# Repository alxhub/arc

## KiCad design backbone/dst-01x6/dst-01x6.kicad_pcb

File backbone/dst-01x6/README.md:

# ARC-DST-01x6

ARC-DST-01x6 drives six independent track districts from the layout's track supply. It receives DCC timing over the ARC backbone, while CAN carries commands and reports each district's state.

Each district can drive normal train traffic or a programming track at a lower current limit. The board measures its total track current and each district's current, so ARC can identify an overloaded section. Two temperature sensors and a controlled fan support sustained operation.

The six district board serves larger sections of a layout with one controller and one backbone connection. Its link is electrically isolated from the track supply, and its DC input protects against a reversed field connection.

[Board design](board.kdl)
[PCB layout](dst-01x6.kicad_pcb)

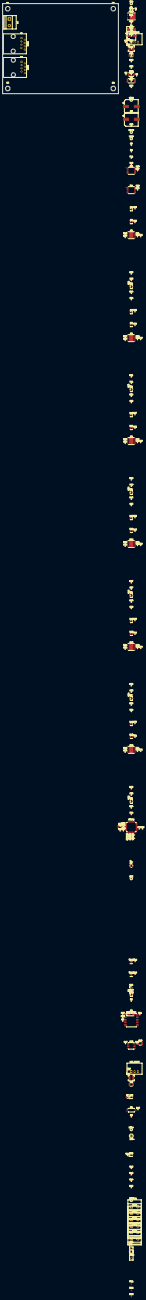
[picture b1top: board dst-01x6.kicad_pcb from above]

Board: 4 copper layers, 90.0 x 70.0 mm, 216 parts (0 on the bottom side), 142 nets, no tracks yet.

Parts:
3V3_BUCK: R-78K3.3-0.5; Converter_DCDC_RECOM_R-78K-0.5_THT
C1, C33, C41, C49, C57, C65, C73: 10nF; C_0402_1005Metric
C2: 47µF; CP_Elec_6.3x7.7
C3, C4, C15: 10µF; C_1210_3225Metric
C5, C37, C45, C53, C61, C69, C77: 1nF; C_0402_1005Metric
C6, C9, C10, C11, C12, C13, C14, C17, C18, C20, C21, C22, C24, C26, C27, C30, C32, C34, C35, C36, C38, C40, C42, C43, C44, C46, C48, C50, C51, C52, C54, C56, C58, C59, C60, C62, C64, C66, C67, C68, C70, C72, C74, C75, C76: 100nF; C_0402_1005Metric
C7, C8: 220µF; CP_Elec_10x16.5
C16, C19, C23: 4.7µF; C_1210_3225Metric
C25: 1µF; C_1210_3225Metric
C28, C29: 1µF; C_0402_1005Metric
C31, C39, C47, C55, C63, C71: 22nF; C_0402_1005Metric
CAN: ISO1044BD; SOIC-8_3.9x4.9mm_P1.27mm
D1: SMBJ18A; D_SMB
D2: SS14; D_SMA
DC: Conn_01x02; TerminalBlock_Phoenix_MKDS-1,5-2-5.08_1x02_P5.08mm_Horizont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
DCC: TestPoint; TestPoint_Pad_D1.5mm
DCC_SYNC: ISO1430DW; SOIC-16W_7.5x10.3mm_P1.27mm
FAN: Conn_01x02; PinHeader_1x02_P2.54mm_Vertical
FID1, FID2, FID3: Fiducial; Fiducial_1mm_Mask2mm
GND: TestPoint; TestPoint_Loop_D2.50mm_Drill1.0mm
H1, H2, H3, H4: MountingHole; MountingHole_3.5mm
HSE: TestPoint; TestPoint_Pad_D1.5mm
IO0, IO1: TCA9534; TSSOP-16_4.4x5mm_P0.65mm
L1: 100µH; L_Bourns-SRN4018
L2: 15µH; L_Bourns-SRN4018
LNK: green; LED_0805_2012Metric
LNK1, LNK2: RJ45; RJ45_Amphenol_54602-x08_Horizontal
LNK+: TestPoint; TestPoint_Pad_D1.5mm
LNK-: TestPoint; TestPoint_Loop_D2.50mm_Drill1.0mm
LNK_BUCK: R-78E5.0-0.5; Converter_DCDC_RECOM_R-78E-0.5_THT
MON: INA226; TSSOP-10_3x3mm_P0.5mm
PRGM: TestPoint; TestPoint_Pad_D1.5mm
Q1: BSC030N08NS5; TDSON-8-1
Q2: DMN3404L; SOT-23
Q3, Q4, Q5, Q6, Q7, Q8: BSS138; SOT-23
R1: 5mΩ; R_2512_6332Metric
R2, R26, R34, R42, R50, R58, R66: 1kΩ; R_0402_1005Metric
R3: 9.76kΩ; R_0402_1005Metric
R4: 30kΩ; R_0402_1005Metric
R5: 100Ω; R_0402_1005Metric
R6, R8, R19, R27, R35, R43, R51, R59: 10kΩ; R_0402_1005Metric
R7: 300Ω; R_0805_2012Metric
R9: 2kΩ; R_0402_1005Metric
R10, R21, R22, R29, R30, R37, R38, R45, R46, R53, R54, R61, R62: 100kΩ; R_0402_1005Metric
R11: 680Ω; R_0402_1005Metric
R12, R13, R14, R15, R16, R17: 4.7kΩ; R_0402_1005Metric
R18: 33Ω; R_0402_1005Metric
R20, R28, R36, R44, R52, R60: 20kΩ; R_0402_1005Metric
R23, R31, R39, R47, R55, R63: 22.1kΩ; R_0402_1005Metric
R24, R32, R40, R48, R56, R64: 2.49kΩ; R_0402_1005Metric
R25, R33, R41, R49, R57, R65: 22Ω; R_0402_1005Metric
REG: green; LED_0805_2012Metric
SCL: TestPoint; TestPoint_Pad_D1.5mm
SDA: TestPoint; TestPoint_Pad_D1.5mm
STM32: STM32C092CBTx; LQFP-48_7x7mm_P0.5mm
SWD: Conn_01x05; PinHeader_1x05_P2.54mm_Vertical
TEMP0, TEMP1: TMP1075DSG; WSON-8-1EP_2x2mm_P0.5mm_EP0.9x1.6mm
TRK1, TRK2, TRK3, TRK4, TRK5, TRK6: Conn_01x02; TerminalBlock_Phoenix_MKDS-1,5-2-5.08_1x02_P5.08mm_Horizont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
U1: LTC4359-DCB; DFN-6-1EP_3x2mm_P0.5mm_EP1.65x1.35mm
U2: FODM217A; SOP-4_4.4x2.6mm_P1.27mm
U3, U6, U9, U12, U15, U18: DRV8874PWPR; HTSSOP-16-1EP_4.4x5mm_P0.65mm_EP3.4x5mm
U4, U7, U10, U13, U16, U19: 74LVC1G86; SOT-353_SC-70-5
U5, U8, U11, U14, U17, U20: 74LVC1G3157; SOT-363_SC-70-6
VREF: TestPoint; TestPoint_Pad_D1.5mm
VTRK: TestPoint; TestPoint_Pad_D1.5mm
Y1: 40MHz; Oscillator_SMD_ECS_2520MV-xxx-xx-4Pin_2.5x2.0mm

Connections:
DCC: DCC.1, R18.2, STM32.37, U4.1, U7.1, U10.1, U13.1, U16.1, U19.1
DCC_PROG: PRGM.1, STM32.47, U5.3, U8.3, U11.3, U14.3, U17.3, U20.3
DCC_RO: DCC_SYNC.3, R18.1
unnamed: 3V3_BUCK.1, C4.1, C5.1, L1.2
unnamed: LNK.1, R7.1
unnamed: C16.1, L2.2, LNK_BUCK.1
unnamed: Q2.1, R5.2, R6.1
unnamed: C34.2, Q3.3, R24.2
unnamed: C42.2, Q4.3, R32.2
unnamed: C50.2, Q5.3, R40.2
unnamed: C58.2, Q6.3, R48.2
unnamed: C66.2, Q7.3, R56.2
unnamed: C74.2, Q8.3, R64.2
unnamed: R11.1, REG.1
unnamed: Q1.4, U1.2
unnamed: C1.1, U1.5
unnamed: R9.2, U2.1
unnamed: C31.1, U3.13
unnamed: C31.2, U3.14
unnamed: R20.1, U3.7
unnamed: C32.2, U3.12
unnamed: C39.1, U6.13
unnamed: C39.2, U6.14
unnamed: R28.1, U6.7
unnamed: C40.2, U6.12
unnamed: C47.1, U9.13
unnamed: C47.2, U9.14
unnamed: R36.1, U9.7
unnamed: C48.2, U9.12
unnamed: C55.1, U12.13
unnamed: C55.2, U12.14
unnamed: R44.1, U12.7
unnamed: C56.2, U12.12
unnamed: C63.1, U15.13
unnamed: C63.2, U15.14
unnamed: R52.1, U15.7
unnamed: C64.2, U15.12
unnamed: C71.1, U18.13
unnamed: C71.2, U18.14
unnamed: R60.1, U18.7
unnamed: C72.2, U18.12
PHASE0: STM32.2, U4.2
PHASE1: STM32.3, U7.2
PHASE2: STM32.16, U10.2
PHASE3: STM32.22, U13.2
PHASE4: STM32.25, U16.2
PHASE5: STM32.26, U19.2
SIGNAL0: R25.1, U5.4
SIGNAL1: R33.1, U8.4
SIGNAL2: R41.1, U11.4
SIGNAL3: R49.1, U14.4
SIGNAL4: R57.1, U17.4
SIGNAL5: R65.1, U20.4
STREAM0: U4.4, U5.1
STREAM1: U7.4, U8.1
STREAM2: U10.4, U11.1
STREAM3: U13.4, U14.1
STREAM4: U16.4, U17.1
STREAM5: U19.4, U20.1
adc0/adc: C37.1, R26.1, STM32.12
adc1/adc: C45.1, R34.1, STM32.14
adc2/adc: C53.1, R42.1, STM32.15
adc3/adc: C61.1, R50.1, STM32.19
adc4/adc: C69.1, R58.1, STM32.23
adc5/adc: C77.1, R66.1, STM32.28
ctl-pulls/i2c.scl: IO0.14, IO1.14, R15.1, STM32.42
ctl-pulls/i2c.sda: IO0.15, IO1.15, R14.1, STM32.43
d0/A: TRK1.1, U3.8
d0/B: TRK1.2, U3.10
d0/DCC: R25.2, U3.2
d0/ISENSE: C33.1, C34.1, R23.1, R24.1, R26.2, U3.6
d0/PWM: STM32.11, U3.1
d0/nFAULT: R19.1, STM32.1, U3.4
d0/nSLEEP: IO0.4, R21.1, U3.3
d1/A: TRK2.1, U6.8
d1/B: TRK2.2, U6.10
d1/DCC: R33.2, U6.2
d1/ISENSE: C41.1, C42.1, R31.1, R32.1, R34.2, U6.6
d1/PWM: STM32.13, U6.1
d1/nFAULT: R27.1, STM32.4, U6.4
d1/nSLEEP: IO0.5, R29.1, U6.3
d2/A: TRK3.1, U9.8
d2/B: TRK3.2, U9.10
d2/DCC: R41.2, U9.2
d2/ISENSE: C49.1, C50.1, R39.1, R40.1, R42.2, U9.6
d2/PWM: STM32.17, U9.1
d2/nFAULT: R35.1, STM32.18, U9.4
d2/nSLEEP: IO0.6, R37.1, U9.3
d3/A: TRK4.1, U12.8
d3/B: TRK4.2, U12.10
d3/DCC: R49.2, U12.2
d3/ISENSE: C57.1, C58.1, R47.1, R48.1, R50.2, U12.6
d3/PWM: STM32.20, U12.1
d3/nFAULT: R43.1, STM32.21, U12.4
d3/nSLEEP: IO1.4, R45.1, U12.3
d4/A: TRK5.1, U15.8
d4/B: TRK5.2, U15.10
d4/DCC: R57.2, U15.2
d4/ISENSE: C65.1, C66.1, R55.1, R56.1, R58.2, U15.6
d4/PWM: STM32.33, U15.1
d4/nFAULT: R51.1, STM32.24, U15.4
d4/nSLEEP: IO1.5, R53.1, U15.3
d5/A: TRK6.1, U18.8
d5/B: TRK6.2, U18.10
d5/DCC: R65.2, U18.2
d5/ISENSE: C73.1, C74.1, R63.1, R64.1, R66.2, U18.6
d5/PWM: STM32.29, U18.1
d5/nFAULT: R59.1, STM32.32, U18.4
d5/nSLEEP: IO1.6, R61.1, U18.3
dc/DC_IN: DC.1, Q1.1, Q1.2, Q1.3, U1.3, U1.4
dc/GND: 3V3_BUCK.2, C1.2, C2.2, C3.2, C4.2, C6.2, C7.2, C8.2, C9.2, C10.2, C11.2, C12.2, C13.2, C14.2, C17.2, C20.2, C22.2, C23.2, C24.2, C25.2, C26.2, C27.2, C28.2, C29.2, C30.2, C33.2, C35.2, C36.2, C37.2, C38.2, C41.2, C43.2, C44.2, C45.2, C46.2, C49.2, C51.2, C52.2, C53.2, C54.2, C57.2, C59.2, C60.2, C61.2, C62.2, C65.2, C67.2, C68.2, C69.2, C70.2, C73.2, C75.2, C76.2, C77.2, CAN.4, D1.2, DC.2, DCC_SYNC.2, DCC_SYNC.4, DCC_SYNC.8, GND.1, IO0.1, IO0.2, IO0.3, IO0.8, IO1.2, IO1.3, IO1.8, MON.2, MON.7, Q2.2, Q3.2, Q4.2, Q5.2, Q6.2, Q7.2, Q8.2, R4.2, R6.2, R8.2, R11.2, R20.2, R21.2, R22.2, R23.2, R28.2, R29.2, R30.2, R31.2, R36.2, R37.2, R38.2, R39.2, R44.2, R45.2, R46.2, R47.2, R52.2, R53.2, R54.2, R55.2, R60.2, R61.2, R62.2, R63.2, STM32.7, SWD.5, TEMP0.4, TEMP0.5, TEMP0.6, TEMP0.7, TEMP0.9, TEMP1.4, TEMP1.5, TEMP1.6, TEMP1.9, U1.6, U1.7, U2.3, U3.9, U3.15, U3.16, U3.17, U4.3, U5.2, U6.9, U6.15, U6.16, U6.17, U7.3, U8.2, U9.9, U9.15, U9.16, U9.17, U10.3, U11.2, U12.9, U12.15, U12.16, U12.17, U13.3, U14.2, U15.9, U15.15, U15.16, U15.17, U16.3, U17.2, U18.9, U18.15, U18.16, U18.17, U19.3, U20.2, Y1.2
dc/VPWR: C2.1, C3.1, D1.1, D2.1, FAN.1, L1.1, MON.10, Q1.5, R1.1, U1.1
fan/en: R5.1, STM32.40
hse: HSE.1, STM32.8, Y1.3
link/V5_LINK: C18.1, C19.1, C21.1, CAN.8, DCC_SYNC.16, LNK.2, LNK+.1, LNK_BUCK.3, R9.1
link/VLINK: C15.1, L2.1, LNK1.1, LNK1.3, LNK2.1, LNK2.3
link/VLINK_GND: C15.2, C16.2, C18.2, C19.2, C21.2, CAN.7, DCC_SYNC.9, DCC_SYNC.15, LNK1.2, LNK1.6, LNK2.2, LNK2.6, LNK-.1, LNK_BUCK.2, R7.2, U2.2
link/dcc-de: DCC_SYNC.5, R8.1
link/fdcan.rx: CAN.3, STM32.38
link/fdcan.tx: CAN.2, STM32.39
link/good: R10.1, STM32.48, U2.4
link/jacks/CANH: CAN.6, LNK1.4, LNK2.4
link/jacks/CANL: CAN.5, LNK1.5, LNK2.5
link/jacks/DCC_A: DCC_SYNC.12, LNK1.7, LNK2.7
link/jacks/DCC_B: DCC_SYNC.13, LNK1.8, LNK2.8
nALERT: MON.3, R2.1, STM32.44
nINT: IO0.13, IO1.13, R16.1, R17.1
nPROG0: IO0.9, Q3.1, R22.1, U5.6
nPROG1: IO0.10, Q4.1, R30.1, U8.6
nPROG2: IO0.11, Q5.1, R38.1, U11.6
nPROG3: IO1.9, Q6.1, R46.1, U14.6
nPROG4: IO1.10, Q7.1, R54.1, U17.6
nPROG5: IO1.11, Q8.1, R62.1, U20.6
nrst: C24.1, STM32.10, SWD.3
swd/swd.swclk: STM32.36, SWD.2
swd/swd.swdio: STM32.35, SWD.1
thermal/fan/-: D2.2, FAN.2, Q2.3
track/VREF: C11.1, C12.1, R3.2, R4.1, U3.5, U6.5, U9.5, U12.5, U15.5, U18.5, VREF.1
track/VTRK: C7.1, C8.1, C9.1, C10.1, C30.1, C32.1, C38.1, C40.1, C46.1, C48.1, C54.1, C56.1, C62.1, C64.1, C70.1, C72.1, MON.8, MON.9, R1.2, U3.11, U6.11, U9.11, U12.11, U15.11, U18.11, VTRK.1
track/i2c.scl: MON.5, R13.1, SCL.1, STM32.45, TEMP0.2, TEMP1.2
track/i2c.sda: MON.4, R12.1, SDA.1, STM32.46, TEMP0.1, TEMP1.1
track/logic.rail: 3V3_BUCK.3, C5.2, C6.1, C13.1, C14.1, C17.1, C20.1, C22.1, C23.1, C25.1, C26.1, C27.1, C28.1, C29.1, C35.1, C36.1, C43.1, C44.1, C51.1, C52.1, C59.1, C60.1, C67.1, C68.1, C75.1, C76.1, CAN.1, DCC_SYNC.1, DCC_SYNC.6, IO0.16, IO1.1, IO1.16, MON.1, MON.6, R2.2, R3.1, R10.2, R12.2, R13.2, R14.2, R15.2, R16.2, R17.2, R19.2, R27.2, R35.2, R43.2, R51.2, R59.2, REG.2, STM32.5, STM32.6, SWD.4, TEMP0.8, TEMP1.7, TEMP1.8, U4.5, U5.5, U7.5, U8.5, U10.5, U11.5, U13.5, U14.5, U16.5, U17.5, U19.5, U20.5, Y1.1, Y1.4

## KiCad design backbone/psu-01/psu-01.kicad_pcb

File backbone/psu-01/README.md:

# ARC-PSU-01

ARC-PSU-01 supplies the ARC backbone. It takes power from the layout's track supply and switches it onto the cable that serves the other ARC nodes. The switch is off during reset. Firmware closes it automatically after the INA226 monitor responds, then checks the downstream voltage and current before enabling CAN. The DCC line driver also requires a CAN transmit grant. A failed reading or out-of-range voltage/current latches the link off until reset. No CAN command is needed to power the link.

This board is also the usual source of the shared DCC timing signal. It sends that signal to track drivers while CAN carries commands and status between boards. It monitors the power sent onto the backbone and has a light bar for local status.

The firmware repeats a DCC idle packet (`FF 00 FF`) once link power is qualified and layoutd grants transmit permission. Its TIM3 output is driven at 58 µs per half-bit for a `1` and 100 µs per half-bit for a `0`; the line driver stays disabled until both the link reading and transmit permission allow it. A bounded 16-locomotive table cycles 128-step speed packets with an idle packet between rounds and reports each applied state on CAN when it changes and periodically. The board and host simulator both accept valid locomotive throttle frames and send their DCC packets. Command sessions scope sequence numbers; the shared DCC transmit grant persists until MCU restart, without renewal or revocation. DCC readback, console diagnostics, and the light bar also remain to be implemented. DCC timing and fault response still need board-level measurement.

The supply node establishes the backbone's ground reference. Other ARC backbone nodes connect through isolation. A separate USB console provides local diagnostics and setup.

[Board design](board.kdl)
[PCB layout](psu-01.kicad_pcb)

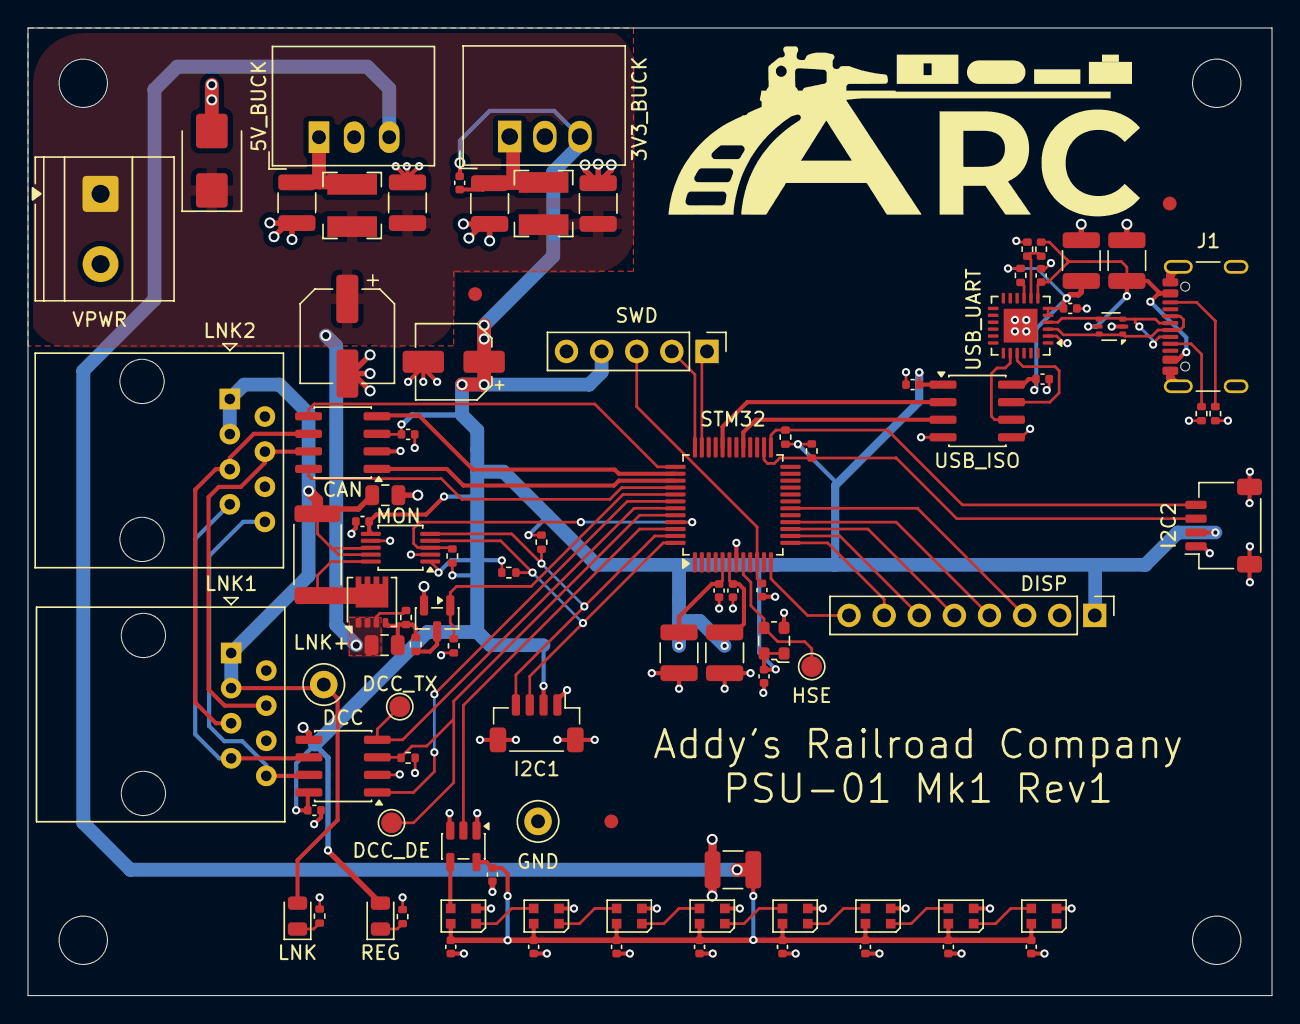
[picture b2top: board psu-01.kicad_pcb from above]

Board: 4 copper layers, 90.0 x 70.0 mm, 97 parts (0 on the bottom side), 61 nets.

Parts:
3V3_BUCK: R-78K3.3-0.5; Converter_DCDC_RECOM_R-78K-0.5_THT
5V_BUCK: R-78E5.0-1.0; Converter_DCDC_RECOM_R-78E-0.5_THT
C1: 47µF; CP_Elec_6.3x7.7
C2, C4: 1µF; C_0805_2012Metric
C3, C10, C11, C12, C13, C14, C15, C16, C17, C18, C20, C21, C22, C24, C26, C27, C29, C31, C33, C34: 100nF; C_0402_1005Metric
C5, C6, C8, C19: 10µF; C_1210_3225Metric
C7: 1nF; C_0402_1005Metric
C9: 2.2µF; C_1210_3225Metric
C23, C25, C30: 4.7µF; C_1210_3225Metric
C28: 10µF; CP_Elec_5x5.8
C32: 1µF; C_1210_3225Metric
CAN: TCAN334G; SOIC-8_3.9x4.9mm_P1.27mm
D1: SMBJ18A; D_SMB
D2, D3, D4, D5, D6, D7, D8, D9: WS2812B-2020; LED_WS2812B-2020_PLCC4_2.0x2.0mm
DCC: ST3485EB; SOIC-8_3.9x4.9mm_P1.27mm
DCC_DE: TestPoint; TestPoint_Pad_D1.5mm
DCC_TX: TestPoint; TestPoint_Pad_D1.5mm
DISP: Conn_01x08; PinHeader_1x08_P2.54mm_Vertical
FID1, FID2, FID3: Fiducial; Fiducial_1mm_Mask2mm
GND: TestPoint; TestPoint_Loop_D2.50mm_Drill1.0mm
H1, H2, H3, H4: MountingHole; MountingHole_3.5mm
HSE: TestPoint; TestPoint_Pad_D1.5mm
I2C1: Conn_01x04_MountingPin; JST_SH_BM04B-SRSS-TB_1x04-1MP_P1.00mm_Vertical
I2C2: Conn_01x04_MountingPin; JST_SH_SM04B-SRSS-TB_1x04-1MP_P1.00mm_Horizontal
J1: USB_C_Receptacle_USB2.0_16P; USB_C_Receptacle_GCT_USB4105-xx-A_16P_TopMnt_Horizontal
L1: 100µH; L_Bourns-SRN4018
L2: 68µH; L_Bourns-SRN4018
LNK: green; LED_0805_2012Metric
LNK1, LNK2: RJ45; RJ45_Amphenol_54602-x08_Horizontal
LNK+: TestPoint; TestPoint_Loop_D2.50mm_Drill1.0mm
LNK_SW: DMP3013SFV; Diodes_PowerDI3333-8
MON: INA226; TSSOP-10_3x3mm_P0.5mm
Q1: BSS138; SOT-23
R1: 49.9kΩ; R_0402_1005Metric
R2, R7, R8: 5.1kΩ; R_0402_1005Metric
R3: 100kΩ; R_0402_1005Metric
R4: 20mΩ; R_2512_6332Metric
R5, R9: 1kΩ; R_0402_1005Metric
R6, R13: 10kΩ; R_0402_1005Metric
R10: 22.1kΩ; R_0402_1005Metric
R11: 47.5kΩ; R_0402_1005Metric
R12: 680Ω; R_0402_1005Metric
R14, R15, R16, R17: 4.7kΩ; R_0402_1005Metric
REG: green; LED_0805_2012Metric
STM32: STM32C092CBTx; LQFP-48_7x7mm_P0.5mm
SWD: Conn_01x05; PinHeader_1x05_P2.54mm_Vertical
U1: 74AHCT1G125; SOT-23-5
U2: USBLC6-2P6; SOT-666
USB_ISO: ISO6721BD; SOIC-8_3.9x4.9mm_P1.27mm
USB_UART: CP2102N-Axx-xQFN24; VQFN-24-1EP_4x4mm_P0.5mm_EP2.45x2.45mm
VPWR: Conn_01x02; TerminalBlock_Phoenix_MKDS-1,5-2-5.08_1x02_P5.08mm_Horizont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
Y1: 40MHz; Oscillator_SMD_ECS_2520MV-xxx-xx-4Pin_2.5x2.0mm

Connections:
3V3: 3V3_BUCK.3, C3.1, C7.2, C20.1, C21.1, C26.1, C28.1, C29.1, C30.1, C32.1, C33.1, C34.1, CAN.3, DCC.8, DISP.1, I2C1.2, I2C2.2, MON.1, MON.6, R5.2, R14.2, R15.2, R16.2, R17.2, REG.2, STM32.5, STM32.6, SWD.4, USB_ISO.1, Y1.1, Y1.4
unnamed: 3V3_BUCK.1, C6.1, C7.1, L1.2
unnamed: 5V_BUCK.1, C9.1, L2.2
unnamed: LNK.1, R13.1
unnamed: Q1.3, R2.1
unnamed: R12.1, REG.1
alert/link: MON.3, R5.1, STM32.45
backbone/port/CANH: CAN.7, LNK1.4, LNK2.4
backbone/port/CANL: CAN.6, LNK1.5, LNK2.5
backbone/port/DCC_A: DCC.6, LNK1.7, LNK2.7
backbone/port/DCC_B: DCC.7, LNK1.8, LNK2.8
bar/5V: 5V_BUCK.3, C10.1, C11.1, C12.1, C13.1, C14.1, C15.1, C16.1, C17.1, C18.1, C19.1, D2.4, D3.4, D4.4, D5.4, D6.4, D7.4, D8.4, D9.4, U1.5
bar/data: STM32.46, U1.2
bar/pixels/DIN: D2.3, U1.4
bar/pixels/p1/out: D2.1, D3.3
bar/pixels/p2/out: D3.1, D4.3
bar/pixels/p3/out: D4.1, D5.3
bar/pixels/p4/out: D5.1, D6.3
bar/pixels/p5/out: D6.1, D7.3
bar/pixels/p6/out: D7.1, D8.3
bar/pixels/p7/out: D8.1, D9.3
can/rxd: CAN.4, STM32.38
can/shdn: CAN.5, STM32.37
can/stb: CAN.8, STM32.40
can/txd: CAN.1, STM32.39
console/3V3_USB: C24.1, C25.1, C27.1, R9.2, USB_ISO.8, USB_UART.5, USB_UART.6
console/USB_GND: C22.2, C23.2, C24.2, C25.2, C27.2, J1.A1, J1.A12, J1.B1, J1.B12, J1.SH, R7.2, R8.2, R11.2, U2.2, USB_ISO.5, USB_UART.2, USB_UART.25
console/VBUS: C22.1, C23.1, J1.A4, J1.A9, J1.B4, J1.B9, R10.1, U2.5, USB_UART.7
console/bridge/bus-powered/rstb: R9.1, USB_UART.9
console/bridge/bus-powered/vbus_sense: R10.2, R11.1, USB_UART.8
console/iso/far-uart.rx: USB_ISO.7, USB_UART.21
console/iso/far-uart.tx: USB_ISO.6, USB_UART.20
console/port/cc1: J1.A5, R7.1
console/port/cc2: J1.B5, R8.1
console/port/usb.dm: J1.A7, J1.B7, U2.3, U2.4, USB_UART.4
console/port/usb.dp: J1.A6, J1.B6, U2.1, U2.6, USB_UART.3
console/rxd: STM32.32, USB_ISO.2
console/txd: STM32.29, USB_ISO.3
dcc/de: DCC.3, DCC_DE.1, R6.1, STM32.44
dcc/rxd: DCC.1, STM32.42
dcc/txd: DCC.4, DCC_TX.1, STM32.43
display/bl: DISP.8, STM32.12
display/clk: DISP.4, STM32.16
display/cs: DISP.5, STM32.15
display/dc: DISP.6, STM32.14
display/din: DISP.3, STM32.18
display/rst: DISP.7, STM32.13
expansion/scl: I2C2.4, R17.1, STM32.25
expansion/sda: I2C2.3, R16.1, STM32.26
hse: HSE.1, STM32.8, Y1.3
nrst: C31.1, STM32.10, SWD.3
rail/GND: 3V3_BUCK.2, 5V_BUCK.2, C1.2, C3.2, C4.2, C5.2, C6.2, C8.2, C9.2, C10.2, C11.2, C12.2, C13.2, C14.2, C15.2, C16.2, C17.2, C18.2, C19.2, C20.2, C21.2, C26.2, C28.2, C29.2, C30.2, C31.2, C32.2, C33.2, C34.2, CAN.2, D1.2, D2.2, D3.2, D4.2, D5.2, D6.2, D7.2, D8.2, D9.2, DCC.2, DCC.5, DISP.2, GND.1, I2C1.1, I2C1.MP, I2C2.1, I2C2.MP, LNK1.2, LNK1.6, LNK2.2, LNK2.6, MON.2, MON.7, Q1.2, R3.2, R6.2, R12.2, R13.2, STM32.7, SWD.5, U1.1, U1.3, USB_ISO.4, VPWR.2, Y1.2
rail/LINK_EN: Q1.1, R3.1, STM32.41
rail/VLINK: C4.1, LNK.2, LNK1.1, LNK1.3, LNK2.1, LNK2.3, LNK+.1, MON.8, MON.9, R4.2
rail/VPWR: C1.1, C2.2, C5.1, C8.1, D1.1, L1.1, L2.1, LNK_SW.1, LNK_SW.2, LNK_SW.3, R1.2, VPWR.1
rail/switch/GATE: C2.1, LNK_SW.4, R1.1, R2.2
rail/switch/out: LNK_SW.5, MON.10, R4.1
screen/scl: I2C1.4, MON.5, R15.1, STM32.47
screen/sda: I2C1.3, MON.4, R14.1, STM32.48
swd/swclk: STM32.36, SWD.2
swd/swdio: STM32.35, SWD.1

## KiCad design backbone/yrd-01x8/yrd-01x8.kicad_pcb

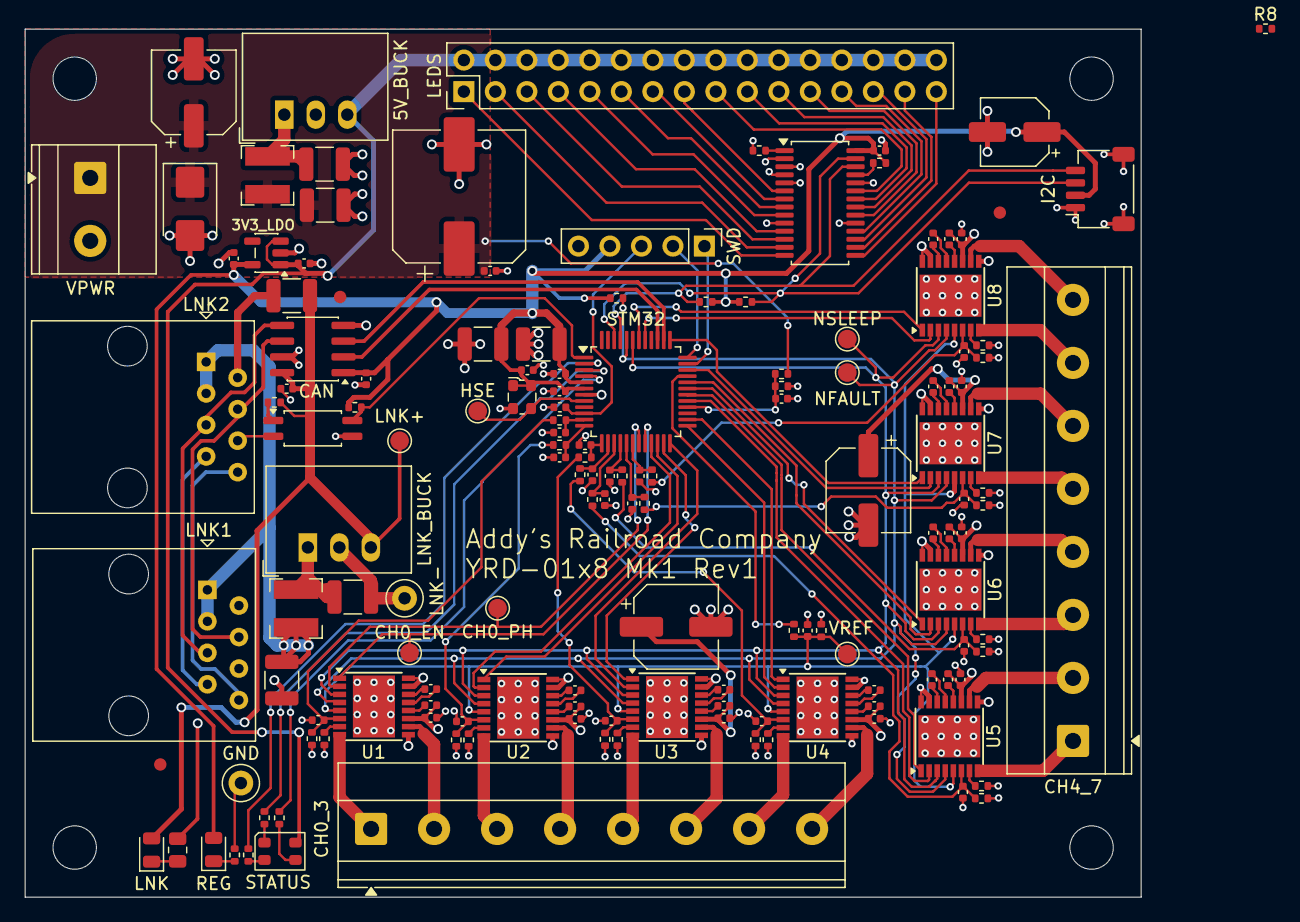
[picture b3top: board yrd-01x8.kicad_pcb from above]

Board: 4 copper layers, 90.0 x 70.0 mm, 151 parts (0 on the bottom side), 134 nets.

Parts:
3V3_LDO: AP2112K-3.3; SOT-23-5
5V_BUCK: R-78E5.0-0.5; Converter_DCDC_RECOM_R-78E-0.5_THT
C1, C44: 10µF; C_1210_3225Metric
C2, C45, C48, C50: 4.7µF; C_1210_3225Metric
C3: 47µF; CP_Elec_6.3x7.7
C4, C5, C10: 1µF; C_0402_1005Metric
C6: 220µF; CP_Elec_10x16.5
C7, C11, C13, C15, C17, C19, C21, C23, C25, C27, C29, C31, C33, C35, C37, C39, C41, C43, C46, C47, C49, C51, C53, C54, C55: 100nF; C_0402_1005Metric
C8, C9: 47µF; CP_Elec_6.3x9.9
C12, C16, C20, C24, C28, C32, C36, C40: 22nF; C_0402_1005Metric
C14, C18, C22, C26, C30, C34, C38, C42: 10nF; C_0402_1005Metric
C52: 1µF; C_1210_3225Metric
C56: 10µF; CP_Elec_5x5.8
C57, C58, C59, C60, C61, C62, C63, C64: 1nF; C_0402_1005Metric
CAN: ISO1044BD; SOIC-8_3.9x4.9mm_P1.27mm
CH0_3, CH4_7: Conn_01x08; TerminalBlock_Phoenix_MKDS-1,5-8-5.08_1x08_P5.08mm_Horizont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
CH0_EN, CH0_PH: TestPoint; TestPoint_Pad_D1.5mm
D1: SMBJ18A; D_SMB
FID1, FID2, FID3: Fiducial; Fiducial_1mm_Mask2mm
GND: TestPoint; TestPoint_Loop_D2.50mm_Drill1.0mm
H1, H2, H3, H4: MountingHole; MountingHole_3.5mm
HSE: TestPoint; TestPoint_Pad_D1.5mm
I2C: Conn_01x04_MountingPin; JST_SH_SM04B-SRSS-TB_1x04-1MP_P1.00mm_Horizontal
L1, L2: 15µH; L_Bourns-SRN4018
LEDS: Conn_02x16_Odd_Even; PinHeader_2x16_P2.54mm_Vertical
LNK: green; LED_0805_2012Metric
LNK1, LNK2: RJ45; RJ45_Amphenol_54602-x08_Horizontal
LNK+: TestPoint; TestPoint_Pad_D1.5mm
LNK-: TestPoint; TestPoint_Loop_D2.50mm_Drill1.0mm
LNK_BUCK: R-78E5.0-0.5; Converter_DCDC_RECOM_R-78E-0.5_THT
NFAULT: TestPoint; TestPoint_Pad_D1.5mm
NSLEEP: TestPoint; TestPoint_Pad_D1.5mm
R1: 680Ω; R_0402_1005Metric
R2: 750Ω; R_0402_1005Metric
R3, R4: 470Ω; R_0402_1005Metric
R5, R7, R26: 10kΩ; R_0402_1005Metric
R6: 1MΩ; R_0402_1005Metric
R8, R29, R30: 100kΩ; R_0402_1005Metric
R9, R11, R13, R15, R17, R19, R21, R23: 20kΩ; R_0402_1005Metric
R10, R12, R14, R16, R18, R20, R22, R24: 1.21kΩ; R_0402_1005Metric
R25: 3.74kΩ; R_0402_1005Metric
R27: 300Ω; R_0805_2012Metric
R28: 2kΩ; R_0402_1005Metric
R31: 18kΩ; R_0402_1005Metric
R32, R33: 4.7kΩ; R_0402_1005Metric
R34, R35, R36, R37, R38, R39, R40, R41: 1kΩ; R_0402_1005Metric
REG: green; LED_0805_2012Metric
STATUS: LED_RGBA; LED_Cree-PLCC4_3.2x2.8mm_CCW
STM32: STM32C092CBTx; LQFP-48_7x7mm_P0.5mm
SWD: Conn_01x05; PinHeader_1x05_P2.54mm_Vertical
U1, U2, U3, U4, U5, U6, U7, U8: DRV8874PWPR; HTSSOP-16-1EP_4.4x5mm_P0.65mm_EP3.4x5mm
U9: TLC59116IPWR; TSSOP-28_4.4x9.7mm_P0.65mm
U10: FODM217A; SOP-4_4.4x2.6mm_P1.27mm
VPWR: Conn_01x02; TerminalBlock_Phoenix_MKDS-1,5-2-5.08_1x02_P5.08mm_Horizont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
VREF: TestPoint; TestPoint_Pad_D1.5mm
Y1: 40MHz; Oscillator_SMD_ECS_2520MV-xxx-xx-4Pin_2.5x2.0mm

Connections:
GND: 3V3_LDO.2, 5V_BUCK.2, C1.2, C2.2, C3.2, C4.2, C5.2, C6.2, C7.2, C8.2, C9.2, C10.2, C11.2, C14.2, C15.2, C18.2, C19.2, C22.2, C23.2, C26.2, C27.2, C30.2, C31.2, C34.2, C35.2, C38.2, C39.2, C42.2, C43.2, C46.2, C49.2, C50.2, C51.2, C52.2, C53.2, C54.2, C55.2, C56.2, C57.2, C58.2, C59.2, C60.2, C61.2, C62.2, C63.2, C64.2, CAN.4, D1.2, GND.1, I2C.1, I2C.MP, R1.2, R6.2, R8.2, R9.2, R10.2, R11.2, R12.2, R13.2, R14.2, R15.2, R16.2, R17.2, R18.2, R19.2, R20.2, R21.2, R22.2, R23.2, R24.2, R25.2, R31.2, STM32.7, SWD.5, U1.9, U1.15, U1.16, U1.17, U2.9, U2.15, U2.16, U2.17, U3.9, U3.15, U3.16, U3.17, U4.9, U4.15, U4.16, U4.17, U5.9, U5.15, U5.16, U5.17, U6.9, U6.15, U6.16, U6.17, U7.9, U7.15, U7.16, U7.17, U8.9, U8.15, U8.16, U8.17, U9.2, U9.3, U9.4, U9.5, U9.10, U9.19, U9.24, U10.3, VPWR.2, Y1.2
unnamed: 5V_BUCK.1, C2.1, L1.2
unnamed: LNK.1, R27.1
unnamed: C45.1, L2.2, LNK_BUCK.1
unnamed: R1.1, REG.1
unnamed: R4.1, STATUS.3
unnamed: R3.1, STATUS.2
unnamed: R2.1, STATUS.1
unnamed: C12.1, U1.13
unnamed: C12.2, U1.14
unnamed: R9.1, U1.7
unnamed: C13.2, U1.12
unnamed: C16.1, U2.13
unnamed: C16.2, U2.14
unnamed: R11.1, U2.7
unnamed: C17.2, U2.12
unnamed: C20.1, U3.13
unnamed: C20.2, U3.14
unnamed: R13.1, U3.7
unnamed: C21.2, U3.12
unnamed: C24.1, U4.13
unnamed: C24.2, U4.14
unnamed: R15.1, U4.7
unnamed: C25.2, U4.12
unnamed: C28.1, U5.13
unnamed: C28.2, U5.14
unnamed: R17.1, U5.7
unnamed: C29.2, U5.12
unnamed: C32.1, U6.13
unnamed: C32.2, U6.14
unnamed: R19.1, U6.7
unnamed: C33.2, U6.12
unnamed: C36.1, U7.13
unnamed: C36.2, U7.14
unnamed: R21.1, U7.7
unnamed: C37.2, U7.12
unnamed: C40.1, U8.13
unnamed: C40.2, U8.14
unnamed: R23.1, U8.7
unnamed: C41.2, U8.12
unnamed: R26.1, U9.25
unnamed: R25.1, U9.1
unnamed: R28.2, U10.1
VPWR: C1.1, C3.1, C6.1, C7.1, C8.1, C9.1, C11.1, C13.1, C15.1, C17.1, C19.1, C21.1, C23.1, C25.1, C27.1, C29.1, C31.1, C33.1, C35.1, C37.1, C39.1, C41.1, D1.1, L1.1, R30.1, U1.11, U2.11, U3.11, U4.11, U5.11, U6.11, U7.11, U8.11, VPWR.1
adc0/adc: C57.1, R34.1, STM32.11
adc1/adc: C58.1, R35.1, STM32.12
adc2/adc: C59.1, R36.1, STM32.13
adc3/adc: C60.1, R37.1, STM32.14
adc4/adc: C61.1, R38.1, STM32.15
adc5/adc: C62.1, R39.1, STM32.16
adc6/adc: C63.1, R40.1, STM32.17
adc7/adc: C64.1, R41.1, STM32.18
hse: HSE.1, STM32.8, Y1.3
link/V5_LINK: C47.1, C48.1, CAN.8, LNK.2, LNK+.1, LNK_BUCK.3, R28.1
link/VLINK: C44.1, L2.1, LNK1.1, LNK1.3, LNK2.1, LNK2.3
link/VLINK_GND: C44.2, C45.2, C47.2, C48.2, CAN.7, LNK1.2, LNK1.6, LNK2.2, LNK2.6, LNK-.1, LNK_BUCK.2, R27.2, U10.2
link/fdcan.rx: CAN.3, STM32.38
link/fdcan.tx: CAN.2, STM32.39
link/good: R29.1, STM32.1, U10.4
link/jacks/CANH: CAN.6, LNK1.4, LNK2.4
link/jacks/CANL: CAN.5, LNK1.5, LNK2.5
link/jacks/DCC_A: LNK1.7, LNK2.7
link/jacks/DCC_B: LNK1.8, LNK2.8
machines/A0: CH0_3.1, U1.8
machines/A1: CH0_3.3, U2.8
machines/A2: CH0_3.5, U3.8
machines/A3: CH0_3.7, U4.8
machines/A4: CH4_7.1, U5.8
machines/A5: CH4_7.3, U6.8
machines/A6: CH4_7.5, U7.8
machines/A7: CH4_7.7, U8.8
machines/B0: CH0_3.2, U1.10
machines/B1: CH0_3.4, U2.10
machines/B2: CH0_3.6, U3.10
machines/B3: CH0_3.8, U4.10
machines/B4: CH4_7.2, U5.10
machines/B5: CH4_7.4, U6.10
machines/B6: CH4_7.6, U7.10
machines/B7: CH4_7.8, U8.10
machines/EN0: CH0_EN.1, STM32.20, U1.1
machines/EN1: STM32.22, U2.1
machines/EN2: STM32.23, U3.1
machines/EN3: STM32.26, U4.1
machines/EN4: STM32.30, U5.1
machines/EN5: STM32.31, U6.1
machines/EN6: STM32.37, U7.1
machines/EN7: STM32.42, U8.1
machines/ISENSE0: C14.1, R10.1, R34.2, U1.6
machines/ISENSE1: C18.1, R12.1, R35.2, U2.6
machines/ISENSE2: C22.1, R14.1, R36.2, U3.6
machines/ISENSE3: C26.1, R16.1, R37.2, U4.6
machines/ISENSE4: C30.1, R18.1, R38.2, U5.6
machines/ISENSE5: C34.1, R20.1, R39.2, U6.6
machines/ISENSE6: C38.1, R22.1, R40.2, U7.6
machines/ISENSE7: C42.1, R24.1, R41.2, U8.6
machines/PH0: CH0_PH.1, STM32.19, U1.2
machines/PH1: STM32.21, U2.2
machines/PH2: STM32.24, U3.2
machines/PH3: STM32.25, U4.2
machines/PH4: STM32.29, U5.2
machines/PH5: STM32.32, U6.2
machines/PH6: STM32.34, U7.2
machines/PH7: STM32.41, U8.2
machines/VREF_PWM: R5.1, STM32.33
machines/logic.rail: 3V3_LDO.5, C5.1, C43.1, C46.1, C49.1, C50.1, C52.1, C53.1, C54.1, C56.1, CAN.1, I2C.2, R7.2, R26.2, R29.2, R32.2, R33.2, REG.2, STM32.5, STM32.6, SWD.4, U9.28, Y1.1, Y1.4
machines/vref: C10.1, R5.2, R6.1, U1.5, U2.5, U3.5, U4.5, U5.5, U6.5, U7.5, U8.5, VREF.1
nFAULT: NFAULT.1, R7.1, STM32.44, U1.4, U2.4, U3.4, U4.4, U5.4, U6.4, U7.4, U8.4
nSLEEP: NSLEEP.1, R8.1, STM32.43, U1.3, U2.3, U3.3, U4.3, U5.3, U6.3, U7.3, U8.3
nrst: C51.1, STM32.10, SWD.3
signals/i2c.scl: I2C.4, R33.1, STM32.45, U9.26
signals/i2c.sda: I2C.3, R32.1, STM32.46, U9.27
signals/lamps.rail: 3V3_LDO.1, 3V3_LDO.3, 5V_BUCK.3, C4.1, LEDS.2, LEDS.4, LEDS.6, LEDS.8, LEDS.10, LEDS.12, LEDS.14, LEDS.16, LEDS.18, LEDS.20, LEDS.22, LEDS.24, LEDS.26, LEDS.28, LEDS.30, LEDS.32, STATUS.4
signals/out0: LEDS.1, U9.14
signals/out1: LEDS.3, U9.13
signals/out2: LEDS.5, U9.12
signals/out3: LEDS.7, U9.11
signals/out4: LEDS.9, U9.9
signals/out5: LEDS.11, U9.8
signals/out6: LEDS.13, U9.7
signals/out7: LEDS.15, U9.6
signals/out8: LEDS.17, U9.23
signals/out9: LEDS.19, U9.22
signals/out10: LEDS.21, U9.21
signals/out11: LEDS.23, U9.20
signals/out12: LEDS.25, U9.18
signals/out13: LEDS.27, U9.17
signals/out14: LEDS.29, U9.16
signals/out15: LEDS.31, U9.15
status/blue: R4.2, STM32.4
status/green: R3.2, STM32.2
status/red: R2.2, STM32.3
supply-sense/tap: C55.1, R30.2, R31.1, STM32.28
swd/swd.swclk: STM32.36, SWD.2
swd/swd.swdio: STM32.35, SWD.1

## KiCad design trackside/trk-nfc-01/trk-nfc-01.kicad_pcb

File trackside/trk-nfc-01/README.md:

# ARC-TRK-NFC-01

ARC-TRK-NFC-01 is a trackside tag reader. It connects to an ARC track hub over a LIN cable and reads NFC tags through a separate antenna flex. The hub can use a tag detection to identify a train or trigger a layout action.

The board powers its reader locally from the track supply. Its controller and reader interface run at the same logic voltage. The cable's 5 V supply continues through the node for other devices on the run.

[Board design](board.kdl)
[PCB layout](trk-nfc-01.kicad_pcb)

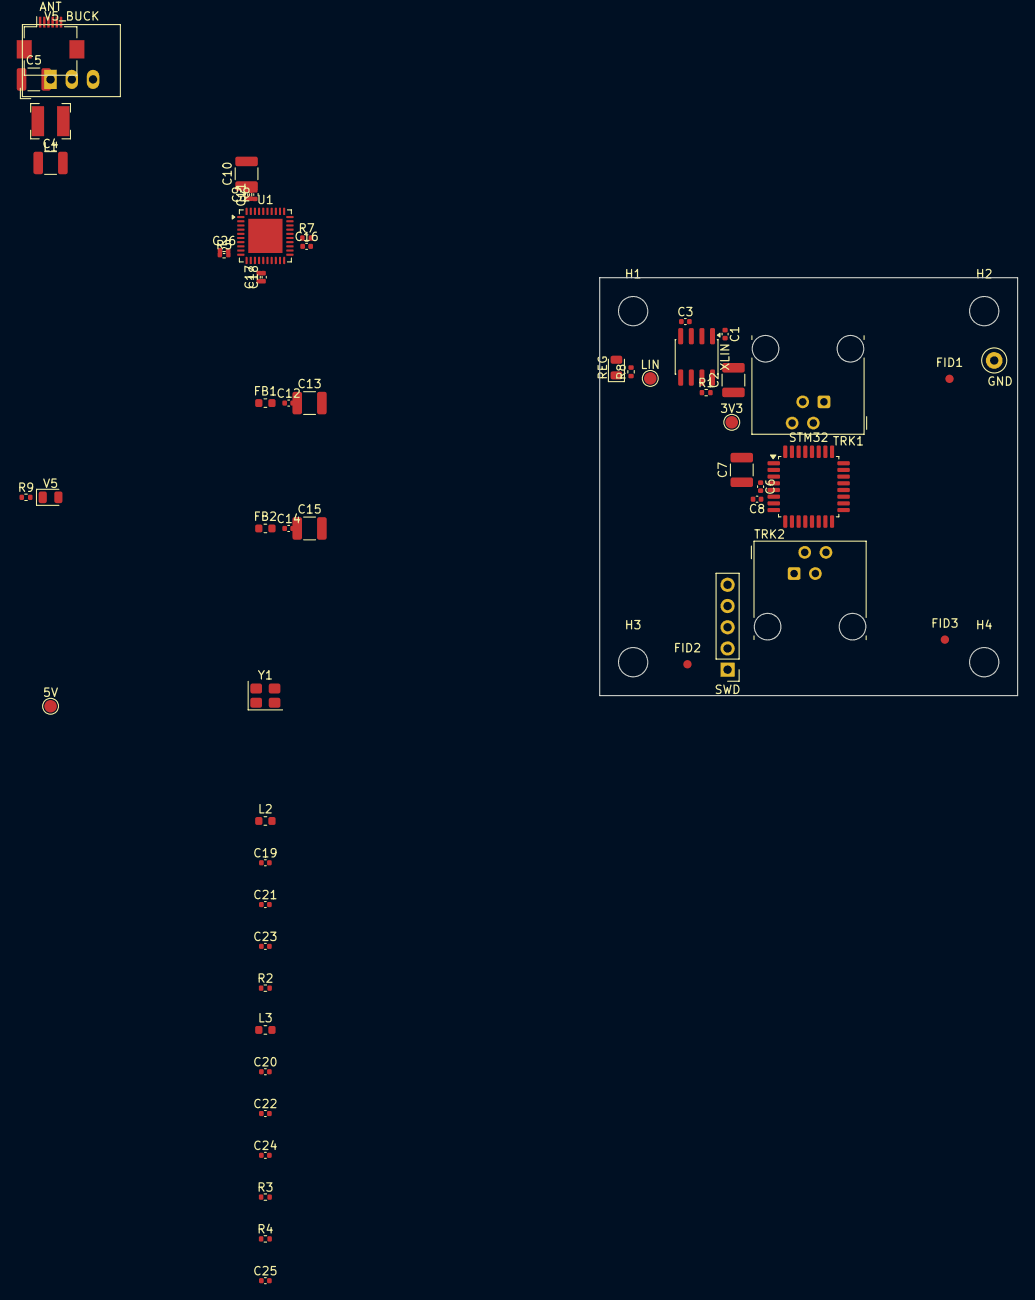
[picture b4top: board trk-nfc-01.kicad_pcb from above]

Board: 2 copper layers, 50.0 x 50.0 mm, 62 parts (0 on the bottom side), 36 nets, no tracks yet.

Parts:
3V3, 5V: TestPoint; TestPoint_Pad_D1.5mm
ANT: Conn_01x06_MountingPin; Hirose_FH12-6S-0.5SH_1x06-1MP_P0.50mm_Horizontal
C1, C6, C8, C9, C11, C12, C14, C16, C26: 100nF; C_0402_1005Metric
C2, C4, C5, C10, C13, C15: 10µF; C_1210_3225Metric
C3, C19, C20: 220pF; C_0402_1005Metric
C7: 4.7µF; C_1210_3225Metric
C17, C18: 15pF; C_0402_1005Metric
C21, C22: 22pF; C_0402_1005Metric
C23, C24: 100pF; C_0402_1005Metric
C25: 1nF; C_0402_1005Metric
FB1, FB2: 600Ω@100MHz; L_0603_1608Metric
FID1, FID2, FID3: Fiducial; Fiducial_1mm_Mask2mm
GND: TestPoint; TestPoint_Loop_D2.50mm_Drill1.0mm
H1, H2, H3, H4: MountingHole; MountingHole_3.5mm
L1: 15µH; L_Bourns-SRN4018
L2, L3: 560nH; L_0603_1608Metric
LIN: TestPoint; TestPoint_Pad_D1.5mm
R1, R6, R7: 10kΩ; R_0402_1005Metric
R2, R3: 1.5Ω; R_0402_1005Metric
R4: 1.8kΩ; R_0402_1005Metric
R5: 1kΩ; R_0402_1005Metric
R8: 680Ω; R_0402_1005Metric
R9: 1.5kΩ; R_0402_1005Metric
REG: green; LED_0805_2012Metric
STM32: STM32C092KBTx; LQFP-32_7x7mm_P0.8mm
SWD: Conn_01x05; PinHeader_1x05_P2.54mm_Vertical
TRK1, TRK2: RJ11; RJ11_Stewart_SS-90000-006_Horizontal
U1: PN5321A3HN_C1xx; HVQFN-40-1EP_6x6mm_P0.5mm_EP4.1x4.1mm
V5: green; LED_0805_2012Metric
V5_BUCK: R-78E5.0-1.0; Converter_DCDC_RECOM_R-78E-0.5_THT
XLIN: NCV7428D13R2G; SOIC-8_3.9x4.9mm_P1.27mm
Y1: 27.12MHz 10pF; Crystal_SMD_3225-4Pin_3.2x2.5mm

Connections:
unnamed: C21.2, C23.1, R2.1
unnamed: C22.2, C24.1, R3.1
unnamed: C19.1, C21.1, L2.2
unnamed: C20.1, C22.1, L3.2, R4.1
unnamed: C25.1, R4.2
unnamed: R8.1, REG.1
unnamed: C14.1, C15.1, FB2.2, U1.8
unnamed: C17.1, U1.14, Y1.1
unnamed: C18.1, U1.15, Y1.3
unnamed: C25.2, R5.1, U1.10
unnamed: C12.1, C13.1, FB1.2, U1.5
unnamed: L2.1, U1.4
unnamed: L3.1, U1.6
unnamed: C26.1, R5.2, U1.9
unnamed: R9.1, V5.1
lin/rxd: STM32.31, XLIN.5
lin/txd: STM32.30, XLIN.6
nfc_irq: R7.1, STM32.7, U1.25
nfc_rst: R6.1, STM32.8, U1.38
node/GND: ANT.MP, C1.2, C2.2, C3.2, C4.2, C5.2, C6.2, C7.2, C8.2, C9.2, C10.2, C11.2, C12.2, C13.2, C14.2, C15.2, C16.2, C17.2, C18.2, C19.2, C20.2, C23.2, C24.2, C26.2, GND.1, R8.2, R9.2, STM32.5, SWD.5, TRK1.4, TRK2.4, U1.1, U1.3, U1.7, U1.11, U1.16, U1.18, U1.41, V5_BUCK.2, XLIN.3, Y1.2, Y1.4
node/LIN: C3.1, LIN.1, TRK1.2, TRK2.2, XLIN.4
node/V5: TRK1.3, TRK2.3
node/VPWR: C1.1, C4.1, L1.1, TRK1.1, TRK2.1, XLIN.1
node/v3v3.rail: 3V3.1, C2.1, C6.1, C7.1, C16.1, R1.2, R6.2, R7.2, REG.2, STM32.4, SWD.4, U1.17, U1.23, XLIN.2, XLIN.8
nrst: C8.1, R1.1, STM32.6, SWD.3, XLIN.7
reader/A: ANT.1, ANT.2, ANT.3, R2.2
reader/B: ANT.4, ANT.5, ANT.6, R3.2
reader/dvdd.rail: C11.1, FB1.1, FB2.1, U1.39
reader/spi-select: STM32.11, U1.27
reader/spi.miso: STM32.13, U1.29
reader/spi.mosi: STM32.14, U1.28
reader/spi.sck: STM32.12, U1.30
swd/swd.swclk: STM32.25, SWD.2
swd/swd.swdio: STM32.24, SWD.1
v5/filtered.rail: C5.1, L1.2, V5_BUCK.1
v5/out.rail: 5V.1, C9.1, C10.1, U1.40, V5.2, V5_BUCK.3
